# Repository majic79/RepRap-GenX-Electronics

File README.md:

# RepRap GenX Electronics

## About
This project contains the hardware schematics and design choices for a low cost printer control board for RepRap hardware. Current boards are very capable, but make decisions on cost and feature set that are not of my choice. By making this available, I aim to add another option out there.

Making the printer control a drop in selection, this will permit re-use of existing driver breakouts (e.g. Pololu A4988's and DRV8825's) and with SPI support for TMC2300 breakouts, it allows an upgrade path. and low cost upgrade potential for existing printer controllers.

__!! Warning - this is still work in progress !!__

This board is based around the ARM MCU STM32F412RGT running at 96MHz in a LQFP-64 package. There are a few free pins, and with some ingenuity, some pins can be multiplexed/multi use.

## Plans

Future intent is to port MarlinFW to this package, from the PlatformIO platform. Programmers for these devices are relatively cheap, but there remains the possibility of a 0 cost programming option via the USB DFU device capabilties.

Selling these individually is not possible in todays marketplace without some additional testing and regulation, but those requirements need to be investigated and addressed as development progresses.

As the majority of components are surface mount (SMD) with only a few through-hole components, the plan is to complete the bill of materials (BOM) for the SMD components and send for professional fabrication on the prototypes.

## Milestones

  * ~~Initial Circuit~~
  * ~~MCU Selection~~
  * ~~Power Supplies~~
  * ~~PCB Layout~~
  * ~~RaspberryPi interface~~ (Abandoned due to lack of space for an interface)
  * ~~5V Power Output (on 2.54mm pitch 2x2 connector)~~
  * Review
  * Feedback
  * Component Selection (BOM)
  * Fabrication
  * Testing
  * Firmware Development

## News

### 2020-01-28
  - Added 3.3v and I2C to the breakout port for possible expansion
  - Shifted E0/E1 Filament sensor feedback to make room for I2C port
  - Adjusted some routes for the 2x4 breakout port

### 2020-01-26
  - Added totem pole drivers for the heater MOSFET's - switching time is <1uS so it should be possible to drive at 1MHz frequency if ever needed
  - Altered heater LED indicators to Red
  - Validated Fan PWM MOSFET's - 4mA is enough to drive at around 4uS which is plenty fast enough and won't overload GPIO pins
  - Altered layout to accomodate new components
  - Split MCU controlled components into their own sheet - not enough space on a single sheet for everything!

### 2020-01-21
  - Abandoned the idea of putting in a Pi Interface - difficult to maintain a 2 layer design and route everything for the 2x20pin GPIO interface of the Pi
  - Added ZVD Ideal diode for 5V output
  - Exposed 5V output (after ZVD) for external consumption (e.g. powering a Pi)
  - Added a copper pour on the top layer for an Earth plane
  - Re-Routed a few signals to maximise covered area on pour
  - Upped trace size for power lines to 0.8mm

### 2020-01-19
	- Initial Commit

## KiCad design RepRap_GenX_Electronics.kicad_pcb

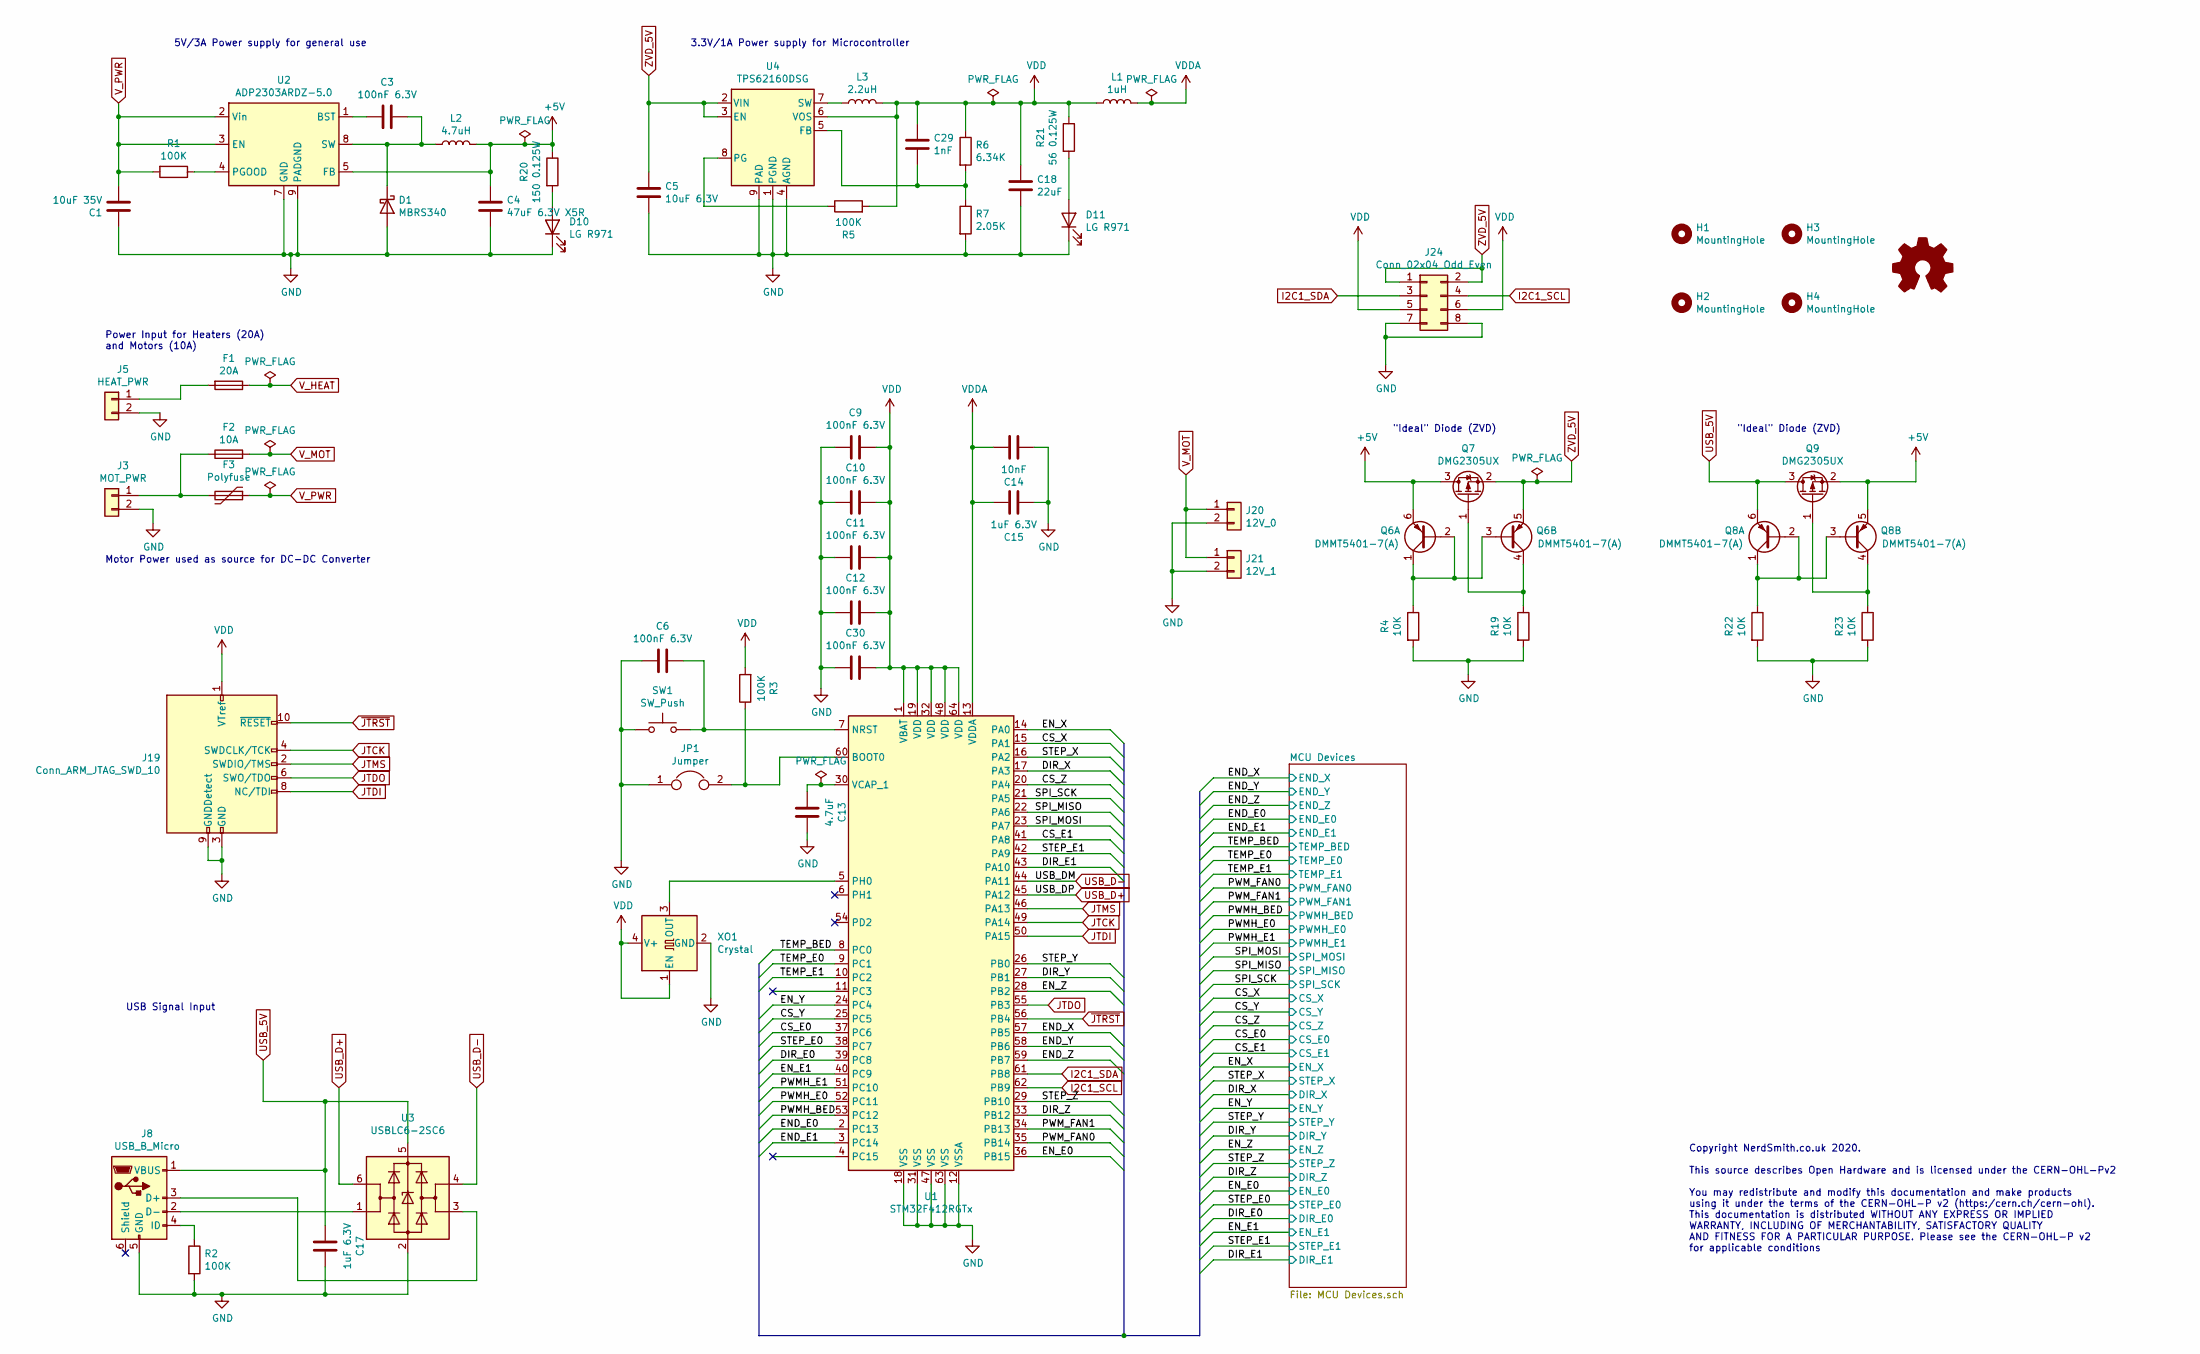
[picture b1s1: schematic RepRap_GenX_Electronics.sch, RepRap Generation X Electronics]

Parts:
C1: 10uF 35V; C_0603_1608Metric
C3, C6, C9, C10, C11, C12, C30: 100nF 6.3V; C_0402_1005Metric
C4: 47uF 6.3V X5R; C_0805_2012Metric; Mfr PartNumber JMK212BBJ476MG-T
C5: 10uF 6.3V; C_0805_2012Metric
C13: 4.7uF; C_0603_1608Metric
C14: 10nF; C_0402_1005Metric
C15, C17: 1uF 6.3V; C_0402_1005Metric
C18: 22uF; C_0603_1608Metric
C29: 1nF; C_0201_0603Metric
D1: MBRS340; D_SMC; Mfr PartNumber MBRS340T3G
D10, D11: LG R971; LED_0805_2012Metric_Castellated
F1: 20A; Fuseholder_Blade_Mini_Keystone_3568
F2: 10A; Fuseholder_Blade_Mini_Keystone_3568
F3: Polyfuse; Fuse_Littelfuse_395Series; Mfr PartNumber RF2624-000
G1: Logo_Open_Hardware_Small; OSHW-Logo2_14.6x12mm_SilkScreen
H1, H2, H3, H4: MountingHole; MountingHole_2.7mm_M2.5_ISO14580
J3: MOT_PWR; TerminalBlock_Phoenix_MKDS-1,5-2-5.08_1x02_P5.08mm_Horizont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
J5: HEAT_PWR; TerminalBlock_Phoenix_MKDS-1,5-2-5.08_1x02_P5.08mm_Horizont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
J8: USB_B_Micro; USB_Micro-B_Molex_47346-0001; Mfr PartNumber 47346-0001
J19: Conn_ARM_JTAG_SWD_10; PinHeader_2x05_P1.27mm_Vertical_SMD; Mfr PartNumber M50-3600542
J20: 12V_0; Molex_KK-254_AE-6410-02A_1x02_P2.54mm_Vertical
J21: 12V_1; Molex_KK-254_AE-6410-02A_1x02_P2.54mm_Vertical
J24: Conn_02x04_Odd_Even; PinHeader_2x04_P2.54mm_Vertical
JP1: Jumper; PinHeader_1x02_P2.54mm_Vertical
L1: 1uH; L_0805_2012Metric; Mfr PartNumber MLZ2012A1R0MT
L2: 4.7uH; L_Taiyo-Yuden_NR-60xx; Mfr PartNumber 74406043047
L3: 2.2uH; L_1008_2520Metric_Pad1.43x2.20mm_HandSolder; Mfr PartNumber VLS252012CX-2R2M-1
Q6, Q8: DMMT5401-7(A); SC-74-6_1.5x2.9mm_P0.95mm; Mfr PartNumber DMMT5401
Q7, Q9: DMG2305UX; SOT-23; Mfr PartNumber DMG2305UX
R1, R2, R3, R5: 100K; R_0603_1608Metric
R4, R19, R22, R23: 10K; R_0603_1608Metric
R6: 6.34K; R_0603_1608Metric
R7: 2.05K; R_0603_1608Metric
R20: 150 0.125W; R_0603_1608Metric
R21: 56 0.125W; R_0603_1608Metric
SW1: SW_Push; SW_SPST_PTS645; Mfr PartNumber PTS645SK43SMTR 92 LFS
U1: STM32F412RGTx; LQFP-64_10x10mm_P0.5mm; Mfr PartNumber STM32F412RGT6
U2: ADP2303ARDZ-5.0; SOIC-8-1EP_3.9x4.9mm_P1.27mm_EP2.29x3mm_ThermalVias; Mfr PartNumber ADP2302ARDZ-5.0
U3: USBLC6-2SC6; SOT-23-6; Mfr PartNumber USBLC6-2SC6
U4: TPS62160DSG; WSON-8-1EP_2x2mm_P0.5mm_EP0.9x1.6mm_ThermalVias; Mfr PartNumber TPS62160DSG
XO1: Crystal; Crystal_SMD_3225-4Pin_3.2x2.5mm; Mfr PartNumber Q33519E40001912

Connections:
+5V: C4.2, L2.2, Q6.6 (E1), Q7.3 (D), Q8.5 (E2), Q9.2 (S), R20.1, U2.5 (FB)
/CS_E0: U1.37 (PC6); also elsewhere on the board
/CS_E1: U1.41 (PA8); also elsewhere on the board
/CS_X: U1.15 (PA1); also elsewhere on the board
/CS_Y: U1.25 (PC5); also elsewhere on the board
/CS_Z: U1.20 (PA4); also elsewhere on the board
/DIR_E0: U1.39 (PC8); also elsewhere on the board
/DIR_E1: U1.43 (PA10); also elsewhere on the board
/DIR_X: U1.17 (PA3); also elsewhere on the board
/DIR_Y: U1.27 (PB1); also elsewhere on the board
/DIR_Z: U1.33 (PB12); also elsewhere on the board
/END_E0: U1.2 (PC13); also elsewhere on the board
/END_E1: U1.3 (PC14); also elsewhere on the board
/END_X: U1.57 (PB5); also elsewhere on the board
/END_Y: U1.58 (PB6); also elsewhere on the board
/END_Z: U1.59 (PB7); also elsewhere on the board
/EN_E0: U1.36 (PB15); also elsewhere on the board
/EN_E1: U1.40 (PC9); also elsewhere on the board
/EN_X: U1.14 (PA0); also elsewhere on the board
/EN_Y: U1.24 (PC4); also elsewhere on the board
/EN_Z: U1.28 (PB2); also elsewhere on the board
/PWMH_BED: U1.53 (PC12); also elsewhere on the board
/PWMH_E0: U1.52 (PC11); also elsewhere on the board
/PWMH_E1: U1.51 (PC10); also elsewhere on the board
/PWM_FAN0: U1.35 (PB14); also elsewhere on the board
/PWM_FAN1: U1.34 (PB13); also elsewhere on the board
/SPI_MISO: U1.22 (PA6); also elsewhere on the board
/SPI_MOSI: U1.23 (PA7); also elsewhere on the board
/SPI_SCK: U1.21 (PA5); also elsewhere on the board
/STEP_E0: U1.38 (PC7); also elsewhere on the board
/STEP_E1: U1.42 (PA9); also elsewhere on the board
/STEP_X: U1.16 (PA2); also elsewhere on the board
/STEP_Y: U1.26 (PB0); also elsewhere on the board
/STEP_Z: U1.29 (PB10); also elsewhere on the board
/TEMP_BED: U1.8 (PC0); also elsewhere on the board
/TEMP_E0: U1.9 (PC1); also elsewhere on the board
/TEMP_E1: U1.10 (PC2); also elsewhere on the board
GND: C1.2, C4.1, C5.2, C6.2, C9.2, C10.2, C11.2, C12.2, C13.1, C14.2, C15.2, C17.1, C18.2, C30.2, D1.2 (A), D10.1 (K), D11.1 (K), J3.2, J5.2, J8.5 (GND), J19.3 (GND), J19.5 (GND), J19.9 (GNDDetect), J20.2, J21.2, J24.7, J24.8, JP1.1, R2.2, R4.2, R7.2, R19.2, R22.2, R23.2, SW1.1, U1.12 (VSSA), U1.18 (VSS), U1.31 (VSS), U1.47 (VSS), U1.63 (VSS), U2.7 (GND), U2.9 (PADGND), U3.2 (GND), U4.1 (PGND), U4.4 (AGND), U4.9 (PAD), XO1.2 (GND); also elsewhere on the board
I2C1_SCL: J24.4, U1.62 (PB9)
I2C1_SDA: J24.3, U1.61 (PB8)
JTCK: J19.4 (SWDCLK/TCK), U1.49 (PA14)
JTDI: J19.8 (NC/TDI), U1.50 (PA15)
JTDO: J19.6 (SWO/TDO), U1.55 (PB3)
JTMS: J19.2 (SWDIO/TMS), U1.46 (PA13)
unnamed: C3.1, U2.1 (BST)
unnamed: C3.2, D1.1 (K), L2.1, U2.8 (SW)
unnamed: C6.1, SW1.2, U1.7 (NRST)
unnamed: C13.2, U1.30 (VCAP_1)
unnamed: C29.2, R6.2, R7.1, U4.5 (FB)
unnamed: D10.2 (A), R20.2
unnamed: D11.2 (A), R21.2
unnamed: F1.2, J5.1
unnamed: F2.1, F3.2, J3.1
unnamed: J8.2 (D-), U3.1 (I/O1)
unnamed: J8.3 (D+), U3.3 (I/O2)
unnamed: J8.4 (ID), R2.1
unnamed: JP1.2, R3.1, U1.60 (BOOT0)
unnamed: L3.1, U4.7 (SW)
unnamed: Q6.1 (C1), Q6.2 (B1), Q6.3 (B2), R4.1
unnamed: Q6.4 (C2), Q7.1 (G), R19.1
unnamed: Q8.1 (C1), Q8.2 (B1), Q8.3 (B2), R22.1
unnamed: Q8.4 (C2), Q9.1 (G), R23.1
unnamed: R1.1, U2.4 (PGOOD)
unnamed: R5.1, U4.8 (PG)
unnamed: U1.5 (PH0), XO1.3 (OUT)
USB_5V: C17.2, J8.1 (VBUS), Q8.6 (E1), Q9.3 (D), U3.5 (VBUS)
USB_D+: U1.45 (PA12), U3.6 (I/O1)
USB_D-: U1.44 (PA11), U3.4 (I/O2)
VDD: C9.1, C10.1, C11.1, C12.1, C18.1, C29.1, C30.1, J19.1 (VTref), J24.5, J24.6, L1.1, L3.2, R3.2, R5.2, R6.1, R21.1, U1.1 (VBAT), U1.19 (VDD), U1.32 (VDD), U1.48 (VDD), U1.64 (VDD), U4.6 (VOS), XO1.1 (EN), XO1.4 (V+); also elsewhere on the board
VDDA: C14.1, C15.1, L1.2, U1.13 (VDDA); also elsewhere on the board
V_HEAT: F1.1; also elsewhere on the board
V_MOT: F2.2, J20.1, J21.1; also elsewhere on the board
V_PWR: C1.1, F3.1, R1.2, U2.2 (Vin), U2.3 (EN)
ZVD_5V: C5.1, J24.1, J24.2, Q6.5 (E2), Q7.2 (S), U4.2 (VIN), U4.3 (EN)
~JTRST: J19.10 (~RESET~), U1.56 (PB4)

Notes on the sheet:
5V/3A Power supply for general use
3.3V/1A Power supply for Microcontroller
USB Signal Input
Power Input for Heaters (20A) and Motors (10A)
Motor Power used as source for DC-DC Converter
"Ideal" Diode (ZVD)
Copyright NerdSmith.co.uk 2020. This source describes Open Hardware and is licensed under the CERN-OHL-Pv2 You may redistribute and modify this documentation and make products using it under the terms of the CERN-OHL-P v2 (https:/cern.ch/cern-ohl). This documentation is distributed WITHOUT ANY EXPR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

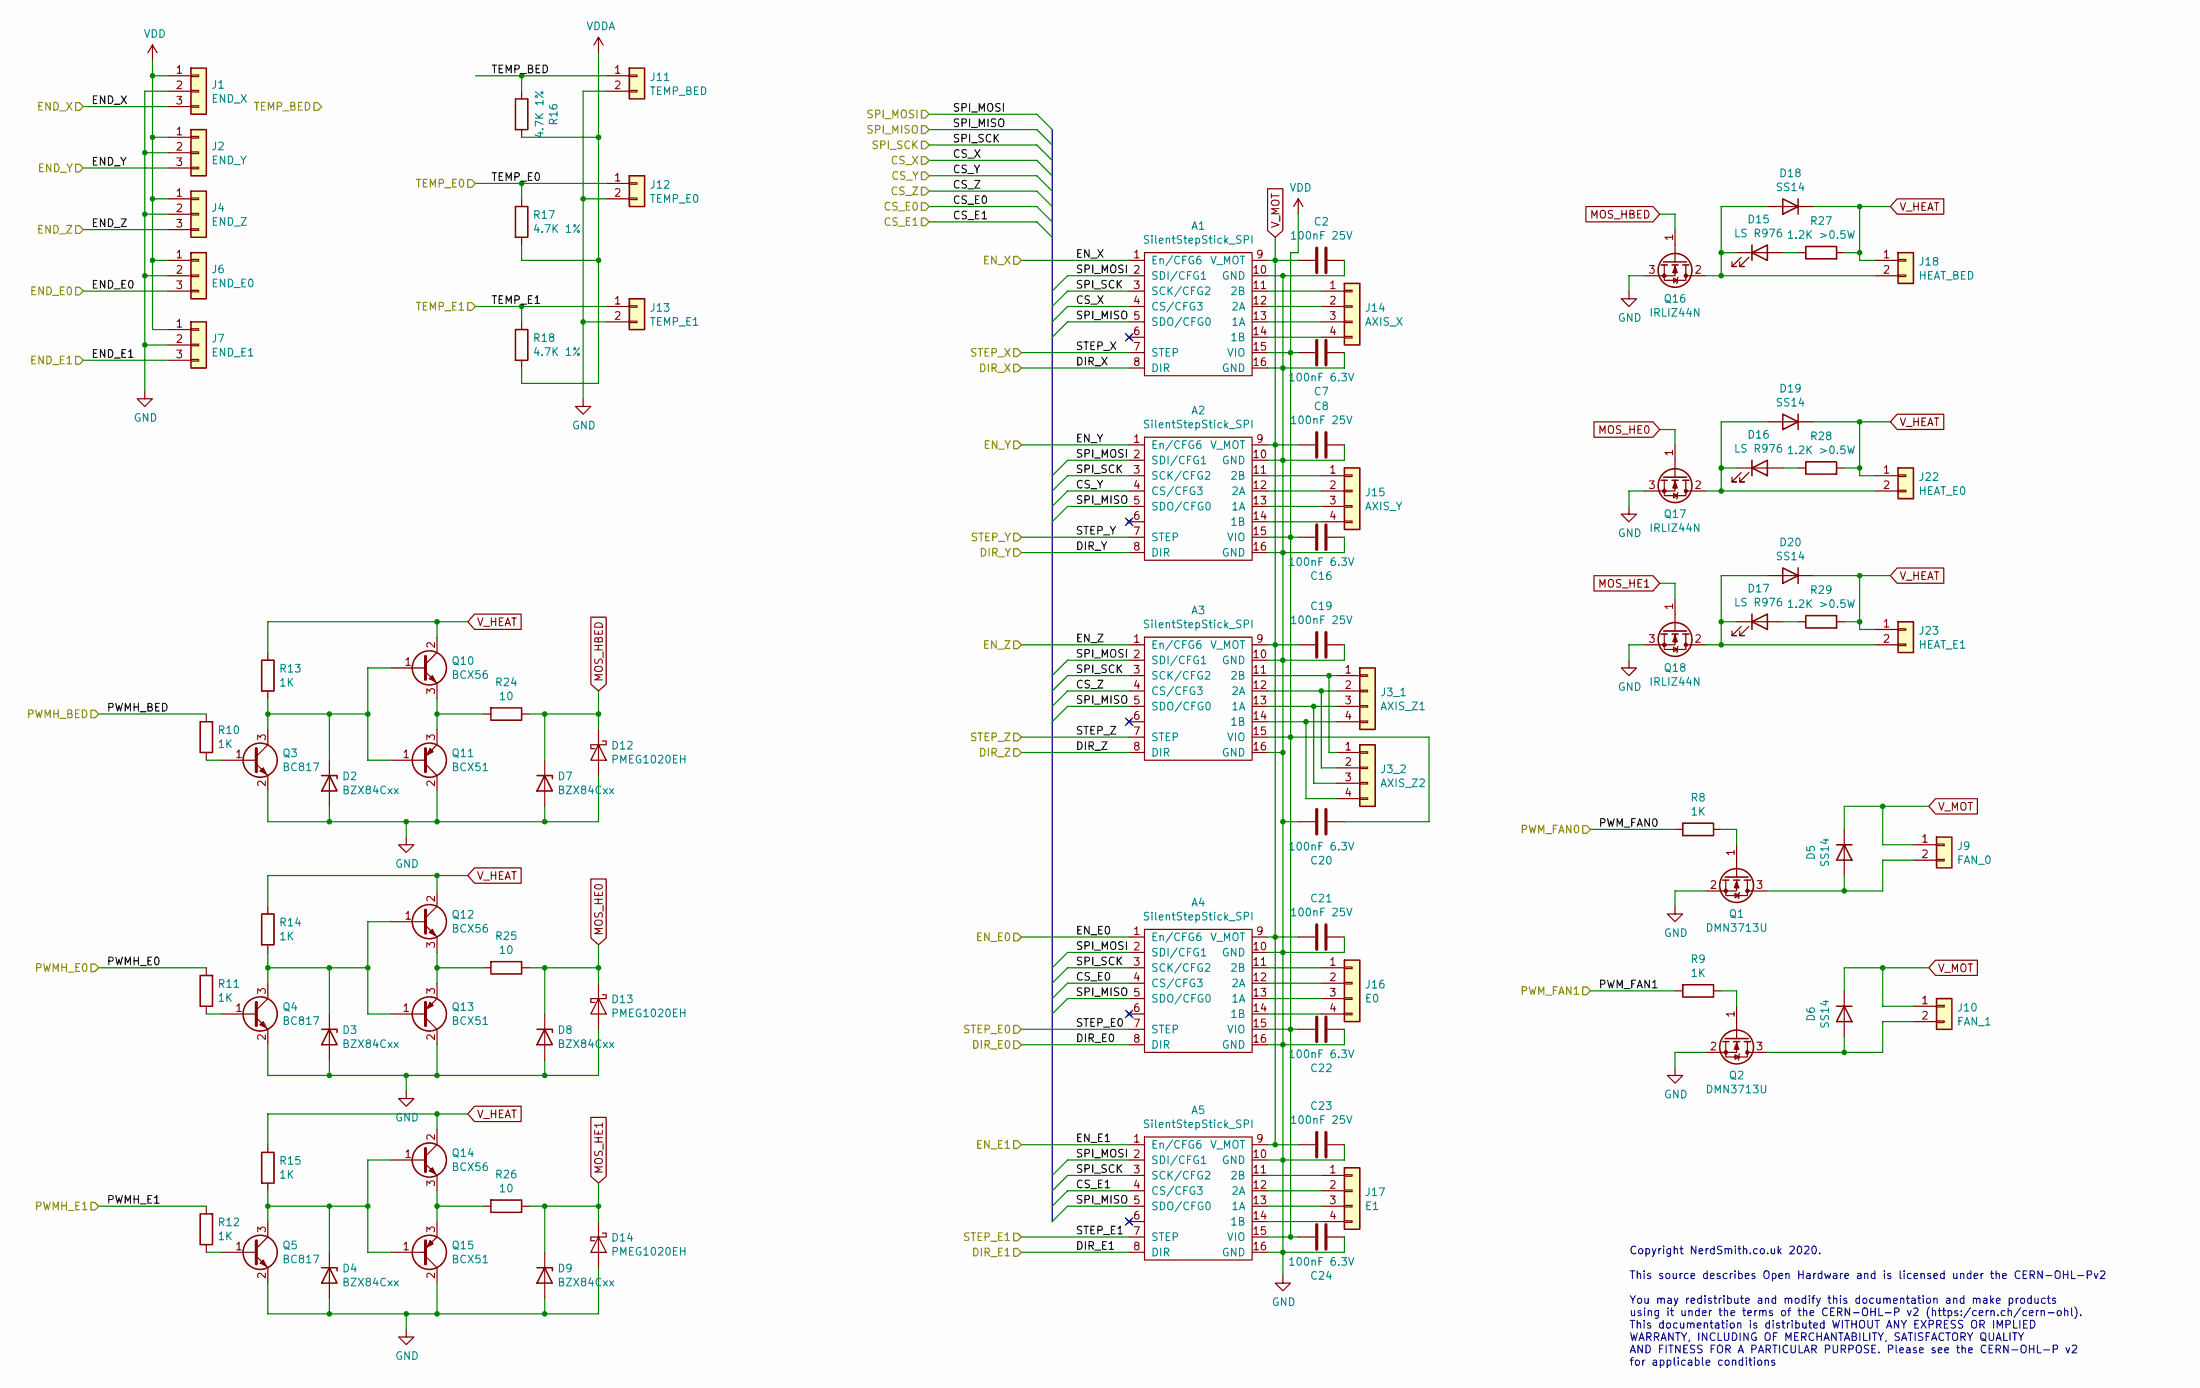
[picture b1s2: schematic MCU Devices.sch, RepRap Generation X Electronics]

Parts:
A1, A2, A3, A4, A5: SilentStepStick_SPI; Pololu_Breakout-16_15.2x20.3mm
C2, C8, C19, C21, C23: 100nF 25V; C_0402_1005Metric
C7, C16, C20, C22, C24: 100nF 6.3V; C_0402_1005Metric
D2, D3, D4, D7, D8, D9: BZX84Cxx; D_SOT-23_ANK
D5, D6, D18, D19, D20: SS14; D_SMA; Mfr PartNumber SS14
D12, D13, D14: PMEG1020EH; D_SOD-123F
D15, D16, D17: LS R976; LED_0805_2012Metric_Castellated
J1: END_X; Molex_KK-254_AE-6410-03A_1x03_P2.54mm_Vertical
J2: END_Y; Molex_KK-254_AE-6410-03A_1x03_P2.54mm_Vertical
J3_1: AXIS_Z1; Molex_KK-254_AE-6410-04A_1x04_P2.54mm_Vertical
J3_2: AXIS_Z2; Molex_KK-254_AE-6410-04A_1x04_P2.54mm_Vertical
J4: END_Z; Molex_KK-254_AE-6410-03A_1x03_P2.54mm_Vertical
J6: END_E0; Molex_KK-254_AE-6410-03A_1x03_P2.54mm_Vertical
J7: END_E1; Molex_KK-254_AE-6410-03A_1x03_P2.54mm_Vertical
J9: FAN_0; Molex_KK-254_AE-6410-02A_1x02_P2.54mm_Vertical
J10: FAN_1; Molex_KK-254_AE-6410-02A_1x02_P2.54mm_Vertical
J11: TEMP_BED; Molex_KK-254_AE-6410-02A_1x02_P2.54mm_Vertical
J12: TEMP_E0; Molex_KK-254_AE-6410-02A_1x02_P2.54mm_Vertical
J13: TEMP_E1; Molex_KK-254_AE-6410-02A_1x02_P2.54mm_Vertical
J14: AXIS_X; Molex_KK-254_AE-6410-04A_1x04_P2.54mm_Vertical
J15: AXIS_Y; Molex_KK-254_AE-6410-04A_1x04_P2.54mm_Vertical
J16: E0; Molex_KK-254_AE-6410-04A_1x04_P2.54mm_Vertical
J17: E1; Molex_KK-254_AE-6410-04A_1x04_P2.54mm_Vertical
J18: HEAT_BED; Molex_KK-396_A-41791-0002_1x02_P3.96mm_Vertical
J22: HEAT_E0; Molex_KK-396_A-41791-0002_1x02_P3.96mm_Vertical
J23: HEAT_E1; Molex_KK-396_A-41791-0002_1x02_P3.96mm_Vertical
Q1, Q2: DMN3713U; SOT-23; Mfr PartNumber DMN3713U
Q3, Q4, Q5: BC817; SOT-23
Q10, Q12, Q14: BCX56; SOT-89-3
Q11, Q13, Q15: BCX51; SOT-89-3
Q16, Q17, Q18: IRLIZ44N; TO-220F-3_Vertical
R8, R9, R10, R11, R12, R13, R14, R15: 1K; R_0805_2012Metric
R16, R17, R18: 4.7K 1%; R_0603_1608Metric
R24, R25, R26: 10; R_0805_2012Metric
R27, R28, R29: 1.2K >0.5W; R_2010_5025Metric

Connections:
/CS_E0: A4.4 (CS/CFG3); also elsewhere on the board
/CS_E1: A5.4 (CS/CFG3); also elsewhere on the board
/CS_X: A1.4 (CS/CFG3); also elsewhere on the board
/CS_Y: A2.4 (CS/CFG3); also elsewhere on the board
/CS_Z: A3.4 (CS/CFG3); also elsewhere on the board
/DIR_E0: A4.8 (DIR); also elsewhere on the board
/DIR_E1: A5.8 (DIR); also elsewhere on the board
/DIR_X: A1.8 (DIR); also elsewhere on the board
/DIR_Y: A2.8 (DIR); also elsewhere on the board
/DIR_Z: A3.8 (DIR); also elsewhere on the board
/END_E0: J6.3; also elsewhere on the board
/END_E1: J7.3; also elsewhere on the board
/END_X: J1.3; also elsewhere on the board
/END_Y: J2.3; also elsewhere on the board
/END_Z: J4.3; also elsewhere on the board
/EN_E0: A4.1 (En/CFG6); also elsewhere on the board
/EN_E1: A5.1 (En/CFG6); also elsewhere on the board
/EN_X: A1.1 (En/CFG6); also elsewhere on the board
/EN_Y: A2.1 (En/CFG6); also elsewhere on the board
/EN_Z: A3.1 (En/CFG6); also elsewhere on the board
/PWMH_BED: R10.2; also elsewhere on the board
/PWMH_E0: R11.2; also elsewhere on the board
/PWMH_E1: R12.2; also elsewhere on the board
/PWM_FAN0: R8.2; also elsewhere on the board
/PWM_FAN1: R9.2; also elsewhere on the board
/SPI_MISO: A1.5 (SDO/CFG0), A2.5 (SDO/CFG0), A3.5 (SDO/CFG0), A4.5 (SDO/CFG0), A5.5 (SDO/CFG0); also elsewhere on the board
/SPI_MOSI: A1.2 (SDI/CFG1), A2.2 (SDI/CFG1), A3.2 (SDI/CFG1), A4.2 (SDI/CFG1), A5.2 (SDI/CFG1); also elsewhere on the board
/SPI_SCK: A1.3 (SCK/CFG2), A2.3 (SCK/CFG2), A3.3 (SCK/CFG2), A4.3 (SCK/CFG2), A5.3 (SCK/CFG2); also elsewhere on the board
/STEP_E0: A4.7 (STEP); also elsewhere on the board
/STEP_E1: A5.7 (STEP); also elsewhere on the board
/STEP_X: A1.7 (STEP); also elsewhere on the board
/STEP_Y: A2.7 (STEP); also elsewhere on the board
/STEP_Z: A3.7 (STEP); also elsewhere on the board
/TEMP_BED: J11.1, R16.1; also elsewhere on the board
/TEMP_E0: J12.1, R17.1; also elsewhere on the board
/TEMP_E1: J13.1, R18.1; also elsewhere on the board
GND: A1.10 (GND), A1.16 (GND), A2.10 (GND), A2.16 (GND), A3.10 (GND), A3.16 (GND), A4.10 (GND), A4.16 (GND), A5.10 (GND), A5.16 (GND), C2.1, C7.2, C8.2, C16.1, C19.2, C20.2, C21.2, C22.1, C23.2, C24.1, D2.2 (A), D3.2 (A), D4.2 (A), D7.2 (A), D8.2 (A), D9.2 (A), D12.2 (A), D13.2 (A), D14.2 (A), J1.2, J2.2, J4.2, J6.2, J7.2, J11.2, J12.2, J13.2, Q1.2 (S), Q2.2 (S), Q3.2 (E), Q4.2 (E), Q5.2 (E), Q11.2 (C), Q13.2 (C), Q15.2 (C), Q16.3 (S), Q17.3 (S), Q18.3 (S); also elsewhere on the board
MOS_HBED: D7.1 (K), D12.1 (K), Q16.1 (G), R24.1
MOS_HE0: D8.1 (K), D13.1 (K), Q17.1 (G), R25.1
MOS_HE1: D9.1 (K), D14.1 (K), Q18.1 (G), R26.1
unnamed: A1.11 (2B), J14.1
unnamed: A1.12 (2A), J14.2
unnamed: A1.13 (1A), J14.3
unnamed: A1.14 (1B), J14.4
unnamed: A2.11 (2B), J15.1
unnamed: A2.12 (2A), J15.2
unnamed: A2.13 (1A), J15.3
unnamed: A2.14 (1B), J15.4
unnamed: A3.11 (2B), J3_1.1, J3_2.1
unnamed: A3.12 (2A), J3_1.2, J3_2.2
unnamed: A3.13 (1A), J3_1.3, J3_2.3
unnamed: A3.14 (1B), J3_1.4, J3_2.4
unnamed: A4.11 (2B), J16.1
unnamed: A4.12 (2A), J16.2
unnamed: A4.13 (1A), J16.3
unnamed: A4.14 (1B), J16.4
unnamed: A5.11 (2B), J17.1
unnamed: A5.12 (2A), J17.2
unnamed: A5.13 (1A), J17.3
unnamed: A5.14 (1B), J17.4
unnamed: D2.1 (K), Q3.3 (C), Q10.1 (B), Q11.1 (B), R13.2
unnamed: D3.1 (K), Q4.3 (C), Q12.1 (B), Q13.1 (B), R14.2
unnamed: D4.1 (K), Q5.3 (C), Q14.1 (B), Q15.1 (B), R15.2
unnamed: D5.2 (A), J9.2, Q1.3 (D)
unnamed: D6.2 (A), J10.2, Q2.3 (D)
unnamed: D15.1 (K), D18.2 (A), J18.2, Q16.2 (D)
unnamed: D15.2 (A), R27.1
unnamed: D16.1 (K), D19.2 (A), J22.2, Q17.2 (D)
unnamed: D16.2 (A), R28.1
unnamed: D17.1 (K), D20.2 (A), J23.2, Q18.2 (D)
unnamed: D17.2 (A), R29.1
unnamed: Q1.1 (G), R8.1
unnamed: Q2.1 (G), R9.1
unnamed: Q3.1 (B), R10.1
unnamed: Q4.1 (B), R11.1
unnamed: Q5.1 (B), R12.1
unnamed: Q10.3 (E), Q11.3 (E), R24.2
unnamed: Q12.3 (E), Q13.3 (E), R25.2
unnamed: Q14.3 (E), Q15.3 (E), R26.2
VDD: A1.15 (VIO), A2.15 (VIO), A3.15 (VIO), A4.15 (VIO), A5.15 (VIO), C7.1, C16.2, C20.1, C22.2, C24.2, J1.1, J2.1, J4.1, J6.1, J7.1; also elsewhere on the board
VDDA: R16.2, R17.2, R18.2; also elsewhere on the board
V_HEAT: D18.1 (K), D19.1 (K), D20.1 (K), J18.1, J22.1, J23.1, Q10.2 (C), Q12.2 (C), Q14.2 (C), R13.1, R14.1, R15.1, R27.2, R28.2, R29.2; also elsewhere on the board
V_MOT: A1.9 (V_MOT), A2.9 (V_MOT), A3.9 (V_MOT), A4.9 (V_MOT), A5.9 (V_MOT), C2.2, C8.1, C19.1, C21.1, C23.1, D5.1 (K), D6.1 (K), J9.1, J10.1; also elsewhere on the board

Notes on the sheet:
Copyright NerdSmith.co.uk 2020. This source describes Open Hardware and is licensed under the CERN-OHL-Pv2 You may redistribute and modify this documentation and make products using it under the terms of the CERN-OHL-P v2 (https:/cern.ch/cern-ohl). This documentation is distributed WITHOUT ANY EXPR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

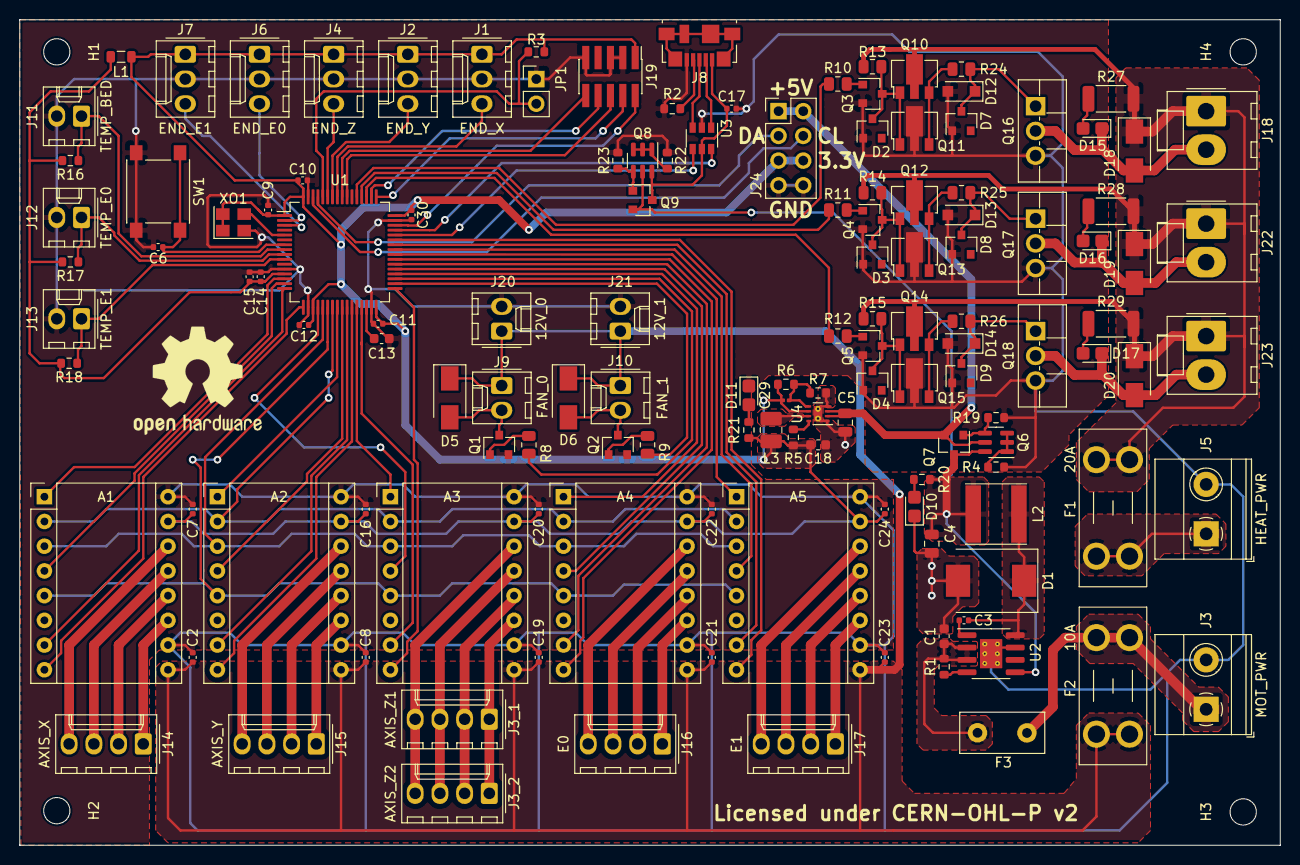
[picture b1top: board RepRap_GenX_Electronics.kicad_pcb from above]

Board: 2 copper layers, 129.5 x 84.8 mm, 142 parts (0 on the bottom side), 117 nets.

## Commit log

2021-01-19 renamed cern_ohl_p_v2.txt to LICENSE and added README.md
2021-01-19 Added 3D render of board
2021-01-19 Added Circuit schematic in more convenient .pdf format
2021-01-19 Added some more "About" as well as target milestones
2021-01-21 Added ZVD and 5V breakout for external supply
2021-01-21 Updated plans to reflect that the Pi Interface won't fit easily
2021-01-26 Added totem pole drivers for MOSFETs and split main schematic
2021-01-27 Added updates to Readme
2021-01-28 Added I2C and 3.3v breakout for expansion port

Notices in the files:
MCU Devices.sch:
Copyright (C) 2021 nerdsmith.co.uk
RepRap_GenX_Electronics.kicad_pcb:
Licensed under CERN-OHL-P v2
